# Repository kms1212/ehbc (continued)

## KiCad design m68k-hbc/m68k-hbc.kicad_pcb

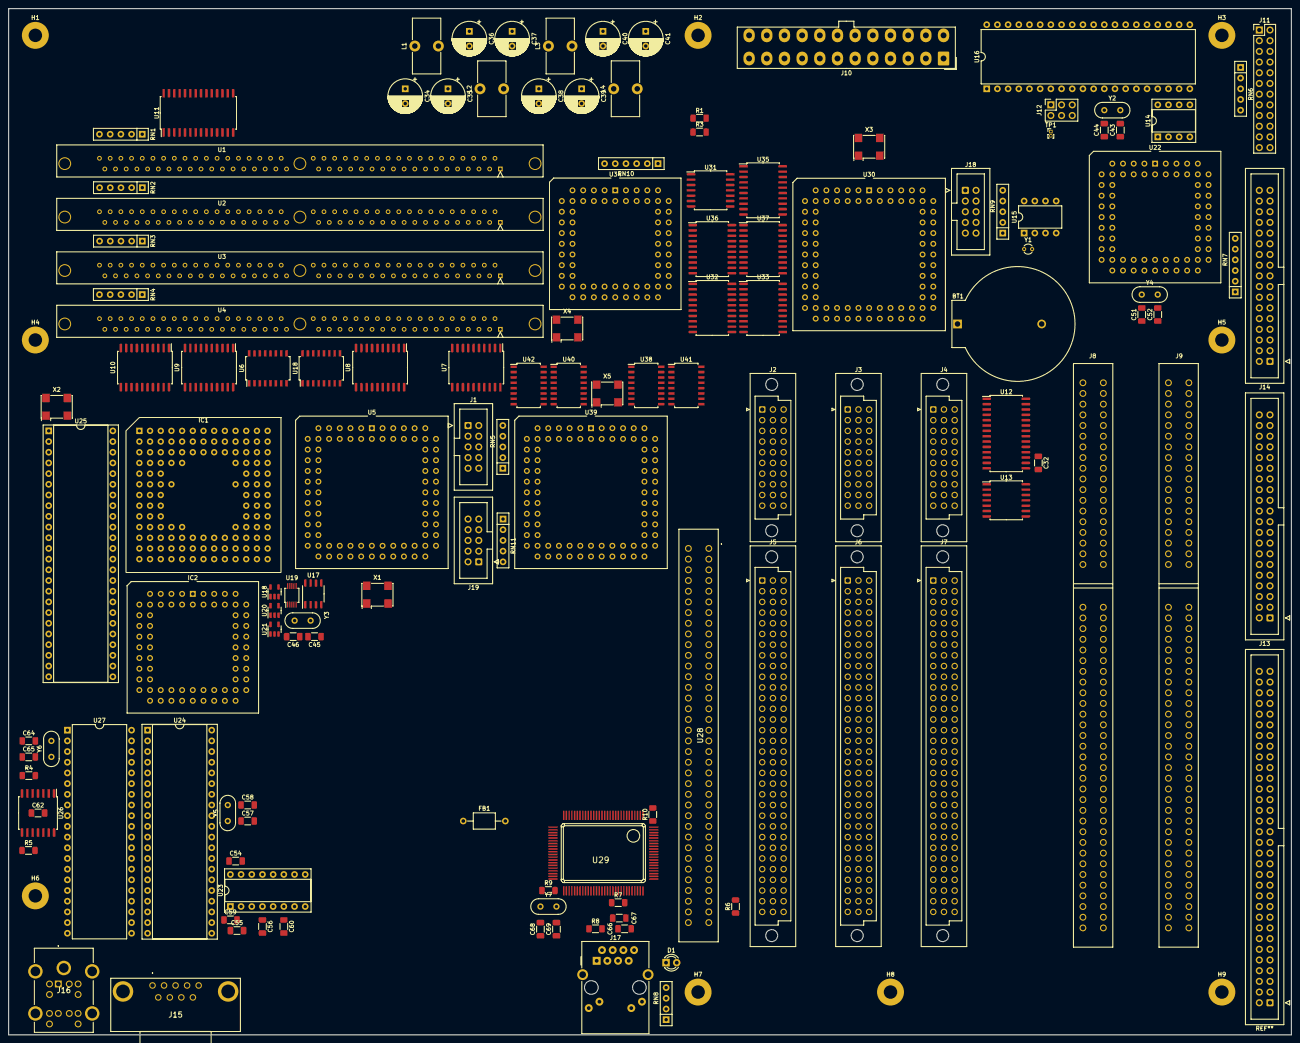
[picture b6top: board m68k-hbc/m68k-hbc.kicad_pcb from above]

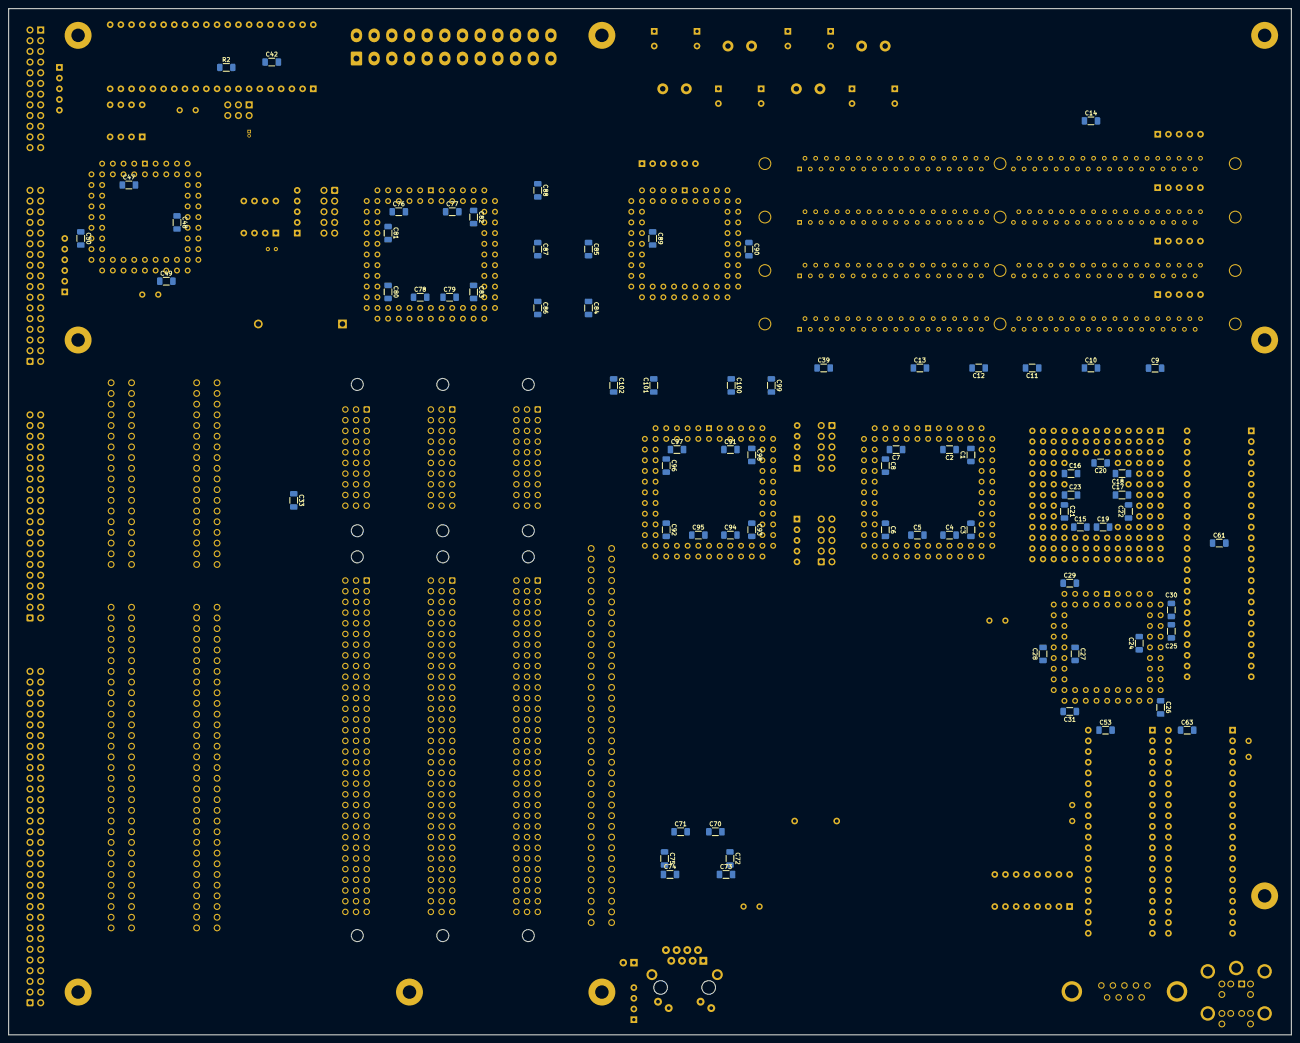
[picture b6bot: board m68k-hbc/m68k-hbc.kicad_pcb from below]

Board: 6 copper layers, 304.8 x 243.8 mm, 217 parts (75 on the bottom side), 360 nets, no tracks yet.

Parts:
BT1: Battery_Cell; BatteryHolder_ComfortableElectronic_CH273-2450_1x2450
C1, C2, C3, C4, C5, C6, C7, C8, C9, C10, C11, C12, C13, C14, C15, C16, C17, C18, C19, C20, C21, C22, C23, C24, C25, C26, C27, C28, C29, C30, C31, C32, C33, C39#2, C42, C47, C48, C49, C50, C53, C61, C62, C63, C76, C77, C78, C79, C80, C81, C82, C83, C84, C85, C86, C87, C88, C89, C90, C91, C92, C93, C94, C95, C96, C97, C98, C99, C100, C101, C102: 100p; C_1206_3216Metric_Pad1.33x1.80mm_HandSolder
C34, C36, C38, C40: 470u; CP_Radial_D8.0mm_P3.50mm
C35, C37, C39, C41: 47u; CP_Radial_D8.0mm_P3.50mm
C43, C44, C45, C46, C68, C69: 22p; C_1206_3216Metric_Pad1.33x1.80mm_HandSolder
C51, C52, C57, C58: 10p; C_1206_3216Metric_Pad1.33x1.80mm_HandSolder
C54, C55, C56, C59, C60: 1u; C_1206_3216Metric_Pad1.33x1.80mm_HandSolder
C64, C65: 20p; C_1206_3216Metric_Pad1.33x1.80mm_HandSolder
C66, C67: 10n; C_1206_3216Metric_Pad1.33x1.80mm_HandSolder
C70, C71, C72, C73, C74, C75: 100n; C_1206_3216Metric_Pad1.33x1.80mm_HandSolder
D1: LED; LED_D3.0mm
FB1: FerriteBead; L_Axial_L5.0mm_D3.6mm_P10.00mm_Horizontal_Murata_BL01RN1A2A2
H1, H2, H3, H4, H5, H6, H7, H8, H9: M3_MH_Pad; MountingHole_3.2mm_M3_Pad
IC1: MC68030RC; PGA128
IC2: MC68881FN; PLCC-68_THT-Socket
J1: JTAG_DRAMC; IDC-Header_2x05_P2.54mm_Vertical
J2, J3, J4: PEP_Power_DIN41612_3x10; DIN41612_C3_3x10_Female_Vertical_THT
J5, J6, J7: PEP_Data_DIN41612_3x32; DIN41612_C_3x32_Female_Vertical_THT
J8, J9: Bus_ISA_16bit; ISA_16bit
J10: ATX-24; Molex_Mini-Fit_Jr_5566-24A_2x12_P4.20mm_Vertical
J11: Conn_02x12_Odd_Even; PinHeader_2x12_P2.54mm_Vertical
J12: ICSP_SMC; PinSocket_2x03_P2.54mm_Vertical
J13: IDC_PATA; IDC-Header_2x20_P2.54mm_Vertical
J14: IDC_FDD; IDC-Header_2x17_P2.54mm_Vertical
J15: 5747840-4; 57478404
J16: KMDGX-6SG_P-S4N; KMDGX6SGPS4N
J17: RJ45_Amphenol_RJMG1BD3B8K1ANR
J18: JTAG_PIC; IDC-Header_2x05_P2.54mm_Vertical
J19: JTAG_ADDEC; IDC-Header_2x05_P2.54mm_Vertical
L1, L2, L3, L4: 10u; L_Toroid_Vertical_L13.0mm_W6.5mm_P5.60mm
R1, R2, R4, R5, R6, R7: 10k; R_1206_3216Metric_Pad1.30x1.75mm_HandSolder
R3: 200k; R_1206_3216Metric_Pad1.30x1.75mm_HandSolder
R8: 200; R_1206_3216Metric_Pad1.30x1.75mm_HandSolder
R9: 1M; R_1206_3216Metric_Pad1.30x1.75mm_HandSolder
R10: 27k; R_1206_3216Metric_Pad1.30x1.75mm_HandSolder
RN1, RN2, RN3, RN4: 1k; R_Array_SIP5
RN5, RN6, RN9, RN11: 10k; R_Array_SIP5
RN7, RN10: 1k; R_Array_SIP6
RN8: 330; R_Array_SIP4
TP1: TestPoint_2Pole; PinHeader_1x02_P1.00mm_Vertical
U1: SIMM72 Slot A; SIM72
U2: SIMM72 Slot B; SIM72
U3: SIMM72 Slot C; SIM72
U4: SIMM72 Slot D; SIM72
U5: EPM7128SLC84 / DRAM Controller; PLCC-84_THT-Socket
U6, U18, U38, U40, U42: 74LS137; SOIC-16W_5.3x10.2mm_P1.27mm
U7, U8, U9, U10, U32, U35, U36: 74LS245; SOIC-20W_7.5x12.8mm_P1.27mm
U11, U12: MCP23017_SO; SOIC-28W_7.5x17.9mm_P1.27mm
U13: 74LS02; SOIC-14W_7.5x9mm_P1.27mm
U14: 25LCxxx; DIP-8_W7.62mm_Socket
U15: DS1307+; DIP-8_W7.62mm
U16: ATmegA32-16P; DIP-40_W15.24mm
U17: PCA9306D; SO-8_3.9x4.9mm_P1.27mm
U18#2, U20, U21: SN74LV1T34DBV; SOT-23-5
U19: Si5351A-B-GT; MSOP-10_3x3mm_P0.5mm
U22: PC8477BV; PLCC-68_THT-Socket
U23: MAX232; DIP-16_W7.62mm_Socket
U24: 68681; DIP-40_W15.24mm_Socket
U25: 68230; DIP-48_W15.24mm_Socket
U26: 74LS06; SOIC-14W_7.5x9mm_P1.27mm
U27: VT82C42; DIP-40_W15.24mm
U28: FWMC; 55308438
U29: RTL8019AS
U30: EPM7128SLC84 / Programmable Interrupt Controller; PLCC-84_THT-Socket
U31: 74LS04; SOIC-14W_7.5x9mm_P1.27mm
U33, U37: 74LS573; SOIC-20W_7.5x12.8mm_P1.27mm
U34: MC68440FN; PLCC-68_THT-Socket
U39: EPM7128SLC84 / Address Decoder; PLCC-84_THT-Socket
U41: 74LS139; SOIC-16W_5.3x10.2mm_P1.27mm
X1, X3, X5: 70M; Oscillator_SMD_SeikoEpson_SG8002CA-4Pin_7.0x5.0mm
X2: 8M; Oscillator_SMD_SeikoEpson_SG8002CA-4Pin_7.0x5.0mm
X4: 10M; Oscillator_SMD_SeikoEpson_SG8002CA-4Pin_7.0x5.0mm
Y1: 32.768k; Crystal_Round_D2.0mm_Vertical
Y2: 16M; Crystal_HC52-6mm_Vertical
Y3: 25M; Crystal_HC52-6mm_Vertical
Y4: 24M; Crystal_HC52-6mm_Vertical
Y5: 3.6864M; Crystal_HC52-6mm_Vertical
Y6: 8M; Crystal_HC52-6mm_Vertical
Y7: 20M; Crystal_HC52-6mm_Vertical

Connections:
+3.3V: C41.1, J2.a8 (+3.3V), J2.a9 (+3.3V), J2.b8 (+3.3V), J2.b9 (+3.3V), J2.c8 (+3.3V), J2.c9 (+3.3V), J3.a8 (+3.3V), J3.a9 (+3.3V), J3.b8 (+3.3V), J3.b9 (+3.3V), J3.c8 (+3.3V), J3.c9 (+3.3V), J4.a8 (+3.3V), J4.a9 (+3.3V), J4.b8 (+3.3V), J4.b9 (+3.3V), J4.c8 (+3.3V), J4.c9 (+3.3V), L4.2, U17.2 (VREF1), U19.1 (VDD), U19.7 (VDDO)
+5V: C1.1, C2.1, C3.1, C4.2, C5.2, C6.2, C7.1, C8.2, C9.1, C10.1, C11.1, C12.1, C13.1, C14.2, C15.2, C16.2, C17.1, C18.1, C19.1, C20.1, C21.2, C22.1, C23.2, C24.1, C25.2, C26.1, C27.1, C28.1, C29.1, C30.1, C31.1, C32.2, C33.1, C37.1, C39#2.1, C42.1, C47.1, C48.1, C49.2, C50.2, C53.1, C54.1, C59.1, C61.2, C62.2, C63.1, C70.1, C71.1, C72.2, C73.2, C74.2, C75.1, C76.1, C77.1, C78.2, C79.2, C80.2, C81.2, C82.1, C83.1, C84.1, C85.1, C86.1, C87.1, C88.1, C89.1, C90.2, C91.1, C92.2, C93.1, C94.2, C95.2, C96.2, C97.1, C98.1, C99.1, C100.1, C101.1, C102.1, IC1.C06 (VCC@1), IC1.D04 (VCC@2), IC1.D10 (VCC@3), IC1.F02 (VCC@4), IC1.F11 (VCC@5), IC1.H03 (VCC@6), IC1.H11 (VCC@7), IC1.K04 (VCC@8), IC1.K10 (VCC@9), IC1.L06 (VCC@10), IC2.10 (VCC@1), IC2.16 (VCC@2), IC2.17 (VCC@3), IC2.18 (SIZE), IC2.26 (A0), IC2.27 (VCC@4), IC2.43 (VCC@5), IC2.52 (VCC@6), IC2.53 (VCC@7), IC2.61 (VCC@8), J1.4, J2.a5 (+5V), J2.a6 (+5V), J2.a7 (+5V), J2.b7 (+5V), J2.c5 (+5V), J2.c6 (+5V), J2.c7 (+5V), J3.a5 (+5V), J3.a6 (+5V), J3.a7 (+5V), J3.b7 (+5V), J3.c5 (+5V), J3.c6 (+5V), J3.c7 (+5V), J4.a5 (+5V), J4.a6 (+5V), J4.a7 (+5V), J4.b7 (+5V), J4.c5 (+5V), J4.c6 (+5V), J4.c7 (+5V), J8.3 (+5V), J8.78 (+5V), J9.3 (+5V), J9.78 (+5V), J11.23, J16.A5, J16.B5, J18.4, J19.4, L2.2, R1.1, R3.1, R6.1, RN1.1 (common), RN2.1 (common), RN3.1 (common), RN4.1 (common), RN5.1 (common), RN6.1 (common), RN7.1 (common), RN8.1 (common), RN9.1 (common), RN10.1 (common), RN11.1 (common), TP1.2, U1.10 (+5V), U1.30 (+5V), U1.59 (+5B), U2.10 (+5V), U2.30 (+5V), U2.59 (+5B), U3.10 (+5V), U3.30 (+5V), U3.59 (+5B), U4.10 (+5V), U4.30 (+5V), U4.59 (+5B), U5.3 (VCCINT_2), U5.13 (VCCIO_2), U5.26 (VCCIO_3), U5.38 (VCCIO_4), U5.43 (VCCINT), U5.53 (VCCIO_5), U5.66 (VCCIO_6), U5.78 (VCCIO), U6.6 (G1), U6.16 (VCC), U7.20 (VCC), U8.20 (VCC), U9.20 (VCC), U10.20 (VCC), U11.9 (VDD), U12.9 (VDD), U12.15 (A0), U13.14 (VCC), U14.3 (~WP), U14.7 (~HOLD), U14.8 (VCC), U15.8 (VCC), U18.6 (G1), U18.16 (VCC), U18#2.5 (VCC), U20.5 (VCC), U21.5 (VCC), U22.18 (+5V), U22.27 (IDENT), U22.60 (+5V), U22.68 (+5V), U23.16 (VCC), U24.40 (VCC), U25.12 (VCC), U26.14 (VCC), U27.40 (+5V), U28.1 (+5V), U28.2 (+5V), U28.3 (+5V), U28.4 (+5V), U28.69 (+5V), U28.70 (+5V), U28.71 (+5V), U28.72 (+5V), U29.6 (VDD), U29.15 (SA8), U29.16 (SA9), U29.17 (VDD2), U29.31 (SMEMRB), U29.32 (SMEMWB), U29.47 (VDD3), U29.57 (VDD4), U29.65 (JP), U29.70 (VDD5), U29.89 (VDD6), U30.3 (VCCINT_2), U30.13 (VCCIO_2), U30.26 (VCCIO_3), U30.38 (VCCIO_4), U30.43 (VCCINT), U30.53 (VCCIO_5), U30.66 (VCCIO_6), U30.78 (VCCIO), U31.14 (VCC), U32.20 (VCC), U33.20 (VCC), U34.20 (+5V), U34.55 (+5V), U35.20 (VCC), U36.20 (VCC), U37.20 (VCC), U38.6 (G1), U38.16 (VCC), U39.3 (VCCINT_2), U39.13 (VCCIO_2), U39.26 (VCCIO_3), U39.38 (VCCIO_4), U39.43 (VCCINT), U39.53 (VCCIO_5), U39.66 (VCCIO_6), U39.78 (VCCIO), U40.6 (G1), U40.16 (VCC), U41.16 (VCC), U42.6 (G1), U42.16 (VCC), X1.4 (Vcc), X2.4 (Vcc), X3.4 (Vcc), X4.4 (Vcc), X5.4 (Vcc)
+5VP: C39.1, J2.a4 (+5VSB), J3.a4 (+5VSB), J4.a4 (+5VSB), L3.2, R2.1, U16.10 (VCC)
+12V: C35.1, J2.a2 (+12V), J2.a3 (+12V), J2.b2 (+12V), J2.b3 (+12V), J2.c2 (+12V), J2.c3 (+12V), J3.a2 (+12V), J3.a3 (+12V), J3.b2 (+12V), J3.b3 (+12V), J3.c2 (+12V), J3.c3 (+12V), J4.a2 (+12V), J4.a3 (+12V), J4.b2 (+12V), J4.b3 (+12V), J4.c2 (+12V), J4.c3 (+12V), J8.9 (+12V), J9.9 (+12V), L1.2
+BATT: BT1.1 (+), U15.3 (VBAT)
-5V: J2.c4 (-5V), J3.c4 (-5V), J4.c4 (-5V), J8.5 (-5V), J9.5 (-5V)
-12V: J2.b4 (-12V), J3.b4 (-12V), J4.b4 (-12V), J8.7 (-12V), J9.7 (-12V), J10.14 (-12V)
/ADDEC/ADDEC_TCK: J19.1, RN11.5 (R4), U39.62 (IO/TCK)
/ADDEC/ADDEC_TDI: J19.9, RN11.2 (R1), U39.14 (IO/TDI)
/ADDEC/ADDEC_TDO: J19.3, RN11.4 (R3), U39.71 (IO/TDO)
/ADDEC/ADDEC_TMS: J19.5, RN11.3 (R2), U39.23 (IO/TMS)
/ADDEC/CS0: U38.1 (A0), U39.9 (IO_6), U40.1 (A0), U42.1 (A0)
/ADDEC/CS1: U38.2 (A1), U39.8 (IO_5), U40.2 (A1), U42.2 (A1)
/ADDEC/CS2: U38.3 (A2), U39.6 (IO_4), U40.3 (A2), U42.3 (A2)
/ADDEC/CS3: U39.5 (IO_3), U41.2 (A0)
/ADDEC/CS4: U39.4 (IO_2), U41.3 (A1)
/ADDEC/~CSE: U38.4 (~GL), U39.81 (IO), U40.4 (~GL), U41.1 (E), U42.4 (~GL)
/ADDEC/~DEC0: U38.5 (~G2), U41.4 (O0)
/ADDEC/~DEC1: U40.5 (~G2), U41.5 (O1)
/ADDEC/~DEC2: U41.6 (O2), U42.5 (~G2)
/DMAC/A8/D0: U34.51 (A8/D0), U36.2 (A0), U37.2 (D0)
/DMAC/A9/D1: U34.50 (A9/D1), U36.3 (A1), U37.3 (D1)
/DMAC/A10/D2: U34.49 (A10/D2), U36.4 (A2), U37.4 (D2)
/DMAC/A11/D3: U34.48 (A11/D3), U36.5 (A3), U37.5 (D3)
/DMAC/A12/D4: U34.47 (A12/D4), U36.6 (A4), U37.6 (D4)
/DMAC/A13/D5: U34.46 (A13/D5), U36.7 (A5), U37.7 (D5)
/DMAC/A14/D6: U34.45 (A14/D6), U36.8 (A6), U37.8 (D6)
/DMAC/A15/D7: U34.44 (A15/D7), U36.9 (A7), U37.9 (D7)
/DMAC/A16/D8: U32.2 (A0), U33.2 (D0), U34.43 (A16/D8)
/DMAC/A17/D9: U32.3 (A1), U33.3 (D1), U34.42 (A17/D9)
/DMAC/A18/D10: U32.4 (A2), U33.4 (D2), U34.41 (A18/D10)
/DMAC/A19/D11: U32.5 (A3), U33.5 (D3), U34.40 (A19/D11)
/DMAC/A20/D12: U32.6 (A4), U33.6 (D4), U34.39 (A20/D12)
/DMAC/A21/D13: U32.7 (A5), U33.7 (D5), U34.38 (A21/D13)
/DMAC/A22/D14: U32.8 (A6), U33.8 (D6), U34.37 (A22/D14)
/DMAC/A23/D15: U32.9 (A7), U33.9 (D7), U34.36 (A23/D15)
/DMAC/UAS: U31.2, U33.11 (Load), U37.11 (Load)
/DMAC/~DBEN: RN10.4 (R3), U32.19 (CE), U34.67 (~DBEN), U36.19 (CE)
/DMAC/~DDIR: RN10.5 (R4), U32.1 (A->B), U34.1 (~DDIR), U36.1 (A->B)
/DMAC/~HIBYTE: RN10.6 (R5), U34.66 (~HIBYTE), U35.19 (CE)
/DMAC/~OWN: RN10.2 (R1), U33.1 (OE), U34.64 (~OWN), U37.1 (OE)
/DMAC/~UAS: RN10.3 (R2), U31.1, U34.65 (~UAS)
/DRAM/DRAMC_TCK: J1.1, RN5.5 (R4), U5.62 (IO/TCK)
/DRAM/DRAMC_TDI: J1.9, RN5.2 (R1), U5.14 (IO/TDI)
/DRAM/DRAMC_TDO: J1.3, RN5.4 (R3), U5.71 (IO/TDO)
/DRAM/DRAMC_TMS: J1.5, RN5.3 (R2), U5.23 (IO/TMS)
/DRAM/RASS0: U5.12 (IO_9), U6.1 (A0), U18.1 (A0)
/DRAM/RASS1: U5.11 (IO_8), U6.2 (A1), U18.2 (A1)
/DRAM/RASS2: U5.10 (IO_7), U6.3 (A2), U18.3 (A2)
/DRAM/SA0: U1.12 (A0), U2.12 (A0), U3.12 (A0), U4.12 (A0), U5.68 (IO_51)
/DRAM/SA1: U1.13 (A1), U2.13 (A1), U3.13 (A1), U4.13 (A1), U5.67 (IO_50)
/DRAM/SA2: U1.14 (A2), U2.14 (A2), U3.14 (A2), U4.14 (A2), U5.69 (IO_52)
/DRAM/SA3: U1.15 (A3), U2.15 (A3), U3.15 (A3), U4.15 (A3), U5.70 (IO_53)
/DRAM/SA4: U1.16 (A4), U2.16 (A4), U3.16 (A4), U4.16 (A4), U5.73 (IO_54)
/DRAM/SA5: U1.17 (A5), U2.17 (A5), U3.17 (A5), U4.17 (A5), U5.74 (IO_55)
/DRAM/SA6: U1.18 (A6), U2.18 (A6), U3.18 (A6), U4.18 (A6), U5.75 (IO_56)
/DRAM/SA7: U1.28 (A7), U2.28 (A7), U3.28 (A7), U4.28 (A7), U5.77 (IO_58)
/DRAM/SA8: U1.31 (A8), U2.31 (A8), U3.31 (A8), U4.31 (A8), U5.80 (IO_60)
/DRAM/SA9: U1.32 (A9), U2.32 (A9), U3.32 (A9), U4.32 (A9), U5.81 (IO)
/DRAM/SA10: U1.19 (A10), U2.19 (A10), U3.19 (A10), U4.19 (A10), U5.76 (IO_57)
/DRAM/SA11: U1.29 (A11), U2.29 (A11), U3.29 (A11), U4.29 (A11), U5.79 (IO_59)
/DRAM/SDQ0: U1.2 (DQ0), U2.2 (DQ0), U3.2 (DQ0), U4.2 (DQ0), U7.2 (A0)
/DRAM/SDQ1: U1.4 (DQ1), U2.4 (DQ1), U3.4 (DQ1), U4.4 (DQ1), U7.4 (A2)
/DRAM/SDQ2: U1.6 (DQ2), U2.6 (DQ2), U3.6 (DQ2), U4.6 (DQ2), U7.6 (A4)
/DRAM/SDQ3: U1.8 (DQ3), U2.8 (DQ3), U3.8 (DQ3), U4.8 (DQ3), U7.8 (A6)
/DRAM/SDQ4: U1.20 (DQ4), U2.20 (DQ4), U3.20 (DQ4), U4.20 (DQ4), U8.2 (A0)
/DRAM/SDQ5: U1.22 (DQ5), U2.22 (DQ5), U3.22 (DQ5), U4.22 (DQ5), U8.4 (A2)
/DRAM/SDQ6: U1.24 (DQ6), U2.24 (DQ6), U3.24 (DQ6), U4.24 (DQ6), U8.6 (A4)
/DRAM/SDQ7: U1.26 (DQ7), U2.26 (DQ7), U3.26 (DQ7), U4.26 (DQ7), U8.8 (A6)
/DRAM/SDQ8: U1.49 (DQ8), U2.49 (DQ8), U3.49 (DQ8), U4.49 (DQ8), U9.2 (A0)
/DRAM/SDQ9: U1.51 (DQ9), U2.51 (DQ9), U3.51 (DQ9), U4.51 (DQ9), U9.4 (A2)
/DRAM/SDQ10: U1.53 (DQ10), U2.53 (DQ10), U3.53 (DQ10), U4.53 (DQ10), U9.6 (A4)
/DRAM/SDQ11: U1.55 (DQ11), U2.55 (DQ11), U3.55 (DQ11), U4.55 (DQ11), U9.8 (A6)
/DRAM/SDQ12: U1.57 (DQ12), U2.57 (DQ12), U3.57 (DQ12), U4.57 (DQ12), U10.2 (A0)
/DRAM/SDQ13: U1.61 (DQ13), U2.61 (DQ13), U3.61 (DQ13), U4.61 (DQ13), U10.4 (A2)
/DRAM/SDQ14: U1.63 (DQ14), U2.63 (DQ14), U3.63 (DQ14), U4.63 (DQ14), U10.6 (A4)
/DRAM/SDQ15: U1.65 (DQ15), U2.65 (DQ15), U3.65 (DQ15), U4.65 (DQ15), U10.8 (A6)
/DRAM/SDQ16: U1.3 (DQ16), U2.3 (DQ16), U3.3 (DQ16), U4.3 (DQ16), U7.3 (A1)
/DRAM/SDQ17: U1.5 (DQ17), U2.5 (DQ17), U3.5 (DQ17), U4.5 (DQ17), U7.5 (A3)
/DRAM/SDQ18: U1.7 (DQ18), U2.7 (DQ18), U3.7 (DQ18), U4.7 (DQ18), U7.7 (A5)
/DRAM/SDQ19: U1.9 (DQ19), U2.9 (DQ19), U3.9 (DQ19), U4.9 (DQ19), U7.9 (A7)
/DRAM/SDQ20: U1.21 (DQ20), U2.21 (DQ20), U3.21 (DQ20), U4.21 (DQ20), U8.3 (A1)
/DRAM/SDQ21: U1.23 (DQ21), U2.23 (DQ21), U3.23 (DQ21), U4.23 (DQ21), U8.5 (A3)
/DRAM/SDQ22: U1.25 (DQ22), U2.25 (DQ22), U3.25 (DQ22), U4.25 (DQ22), U8.7 (A5)
/DRAM/SDQ23: U1.27 (DQ23), U2.27 (DQ23), U3.27 (DQ23), U4.27 (DQ23), U8.9 (A7)
/DRAM/SDQ24: U1.50 (DQ24), U2.50 (DQ24), U3.50 (DQ24), U4.50 (DQ24), U9.3 (A1)
/DRAM/SDQ25: U1.52 (DQ25), U2.52 (DQ25), U3.52 (DQ25), U4.52 (DQ25), U9.5 (A3)
/DRAM/SDQ26: U1.54 (DQ26), U2.54 (DQ26), U3.54 (DQ26), U4.54 (DQ26), U9.7 (A5)
/DRAM/SDQ27: U1.56 (DQ27), U2.56 (DQ27), U3.56 (DQ27), U4.56 (DQ27), U9.9 (A7)
/DRAM/SDQ28: U1.58 (DQ28), U2.58 (DQ28), U3.58 (DQ28), U4.58 (DQ28), U10.3 (A1)
/DRAM/SDQ29: U1.60 (DQ29), U2.60 (DQ29), U3.60 (DQ29), U4.60 (DQ29), U10.5 (A3)
/DRAM/SDQ30: U1.62 (DQ30), U2.62 (DQ30), U3.62 (DQ30), U4.62 (DQ30), U10.7 (A5)
/DRAM/SDQ31: U1.64 (DQ31), U2.64 (DQ31), U3.64 (DQ31), U4.64 (DQ31), U10.9 (A7)
/DRAM/~MMAP0: RN1.2 (R1), U1.67 (P0), U11.1 (GPB0)
/DRAM/~MMAP1: RN1.3 (R2), U1.68 (P1), U11.2 (GPB1)
/DRAM/~MMAP2: RN1.4 (R3), U1.69 (P2), U11.3 (GPB2)
/DRAM/~MMAP3: RN1.5 (R4), U1.70 (P3), U11.4 (GPB3)
/DRAM/~MMBP0: RN2.2 (R1), U2.67 (P0), U11.8 (GPB7)
/DRAM/~MMBP1: RN2.3 (R2), U2.68 (P1), U11.7 (GPB6)
/DRAM/~MMBP2: RN2.4 (R3), U2.69 (P2), U11.6 (GPB5)
/DRAM/~MMBP3: RN2.5 (R4), U2.70 (P3), U11.5 (GPB4)
/DRAM/~MMCAS0: U1.40 (~CAS0), U2.40 (~CAS0), U3.40 (~CAS0), U4.40 (~CAS0), U5.4 (IO_2)
/DRAM/~MMCAS1: U1.43 (~CAS1), U2.43 (~CAS1), U3.43 (~CAS1), U4.43 (~CAS1), U5.8 (IO_5)
/DRAM/~MMCAS2: U1.41 (~CAS2), U2.41 (~CAS2), U3.41 (~CAS2), U4.41 (~CAS2), U5.5 (IO_3)
/DRAM/~MMCAS3: U1.42 (~CAS3), U2.42 (~CAS3), U3.42 (~CAS3), U4.42 (~CAS3), U5.6 (IO_4)
/DRAM/~MMCP0: RN3.2 (R1), U3.67 (P0), U11.25 (GPA4)
/DRAM/~MMCP1: RN3.3 (R2), U3.68 (P1), U11.26 (GPA5)
/DRAM/~MMCP2: RN3.4 (R3), U3.69 (P2), U11.27 (GPA6)
/DRAM/~MMCP3: RN3.5 (R4), U3.70 (P3), U11.28 (GPA7)
/DRAM/~MMDP0: RN4.2 (R1), U4.67 (P0), U11.21 (GPA0)
/DRAM/~MMDP1: RN4.3 (R2), U4.68 (P1), U11.22 (GPA1)
/DRAM/~MMDP2: RN4.4 (R3), U4.69 (P2), U11.23 (GPA2)
/DRAM/~MMDP3: RN4.5 (R4), U4.70 (P3), U11.24 (GPA3)
/DRAM/~MMRAS0_A: U1.44 (~RAS0), U1.45 (~RAS2), U6.7 (Y7)
/DRAM/~MMRAS0_B: U2.44 (~RAS0), U2.45 (~RAS2), U6.9 (Y6)
/DRAM/~MMRAS0_C: U3.44 (~RAS0), U3.45 (~RAS2), U6.10 (Y5)
/DRAM/~MMRAS0_D: U4.44 (~RAS0), U4.45 (~RAS2), U6.11 (Y4)
/DRAM/~MMRAS1_A: U1.33 (~RAS3), U1.34 (~RAS1), U6.12 (Y3), U18.7 (Y7)
/DRAM/~MMRAS1_B: U2.33 (~RAS3), U2.34 (~RAS1), U6.13 (Y2), U18.9 (Y6)
/DRAM/~MMRAS1_C: U3.33 (~RAS3), U3.34 (~RAS1), U6.14 (Y1), U18.10 (Y5)
/DRAM/~MMRAS1_D: U4.33 (~RAS3), U4.34 (~RAS1), U6.15 (Y0), U18.11 (Y4)
/DRAM/~RASS_L: U5.15 (IO_10), U6.4 (~GL), U18.4 (~GL)
/Disk/~RD: J13.23 (~DIOW), U22.4 (~RD)
/Disk/~WR: J13.25 (~DIOR), U22.5 (~WR)
/Ethernet/LED0: J17.L3 (LEDG_K), U29.61 (LED0)
/Ethernet/LED1: J17.L2 (LEDY_K), U29.62 (LED1)
/Ethernet/LED2: D1.1 (K), U29.63 (LED2)
/Ethernet/RX+: J17.R3 (RD+), U29.59 (TPIN+)
/Ethernet/RX-: J17.R6 (RD-), U29.58 (TPIN-)
/Ethernet/TX+: J17.R1 (TD+), R8.1, U29.45 (TPOUT+)
/Ethernet/TX-: J17.R2 (TD-), R8.2, U29.46 (TPOUT-)
/FWMEM/~FWMPRES: R6.2, U28.67 (~PRES)
/IO/KBCLK: J16.A6, J16.B6, U26.6, U27.1 (TEST0)
/IO/KBDAT: J16.A1, R5.1, U26.8, U27.27 (P10)
/IO/MSCLK: R4.2, U26.4, U27.39 (TEST1)
/IO/MSDAT: J16.B1, U26.2, U27.28 (P11)
/IO/~DTACK8: U24.9 (DTACK), U25.42 (DTACK)
/PEP/~P0PRESA: J2.b6 (~PRES), U13.2
/PEP/~P0PRESB: J5.a2 (~PRES), U13.3
/PEP/~P0PRES: U12.1 (GPB0), U13.1
/PEP/~P1PRESA: J3.b6 (~PRES), U13.5
/PEP/~P1PRESB: J6.a2 (~PRES), U13.6
/PEP/~P1PRES: U12.2 (GPB1), U13.4
/PEP/~P2PRESA: J4.b6 (~PRES), U13.8
/PEP/~P2PRESB: J7.a2 (~PRES), U13.9
/PEP/~P2PRES: U12.3 (GPB2), U13.10
/PIC/PIC_TCK: J18.1, RN9.5 (R4), U30.62 (IO/TCK)
/PIC/PIC_TDI: J18.9, RN9.2 (R1), U30.14 (IO/TDI)
/PIC/PIC_TDO: J18.3, RN9.4 (R3), U30.71 (IO/TDO)
/PIC/PIC_TMS: J18.5, RN9.3 (R2), U30.23 (IO/TMS)
/Power/+3.3VI: C40.1, J10.1 (+3.3V), J10.2 (+3.3V), J10.12 (+3.3V), J10.13 (+3.3V), L4.1
/Power/+5VI: C36.1, J10.4 (+5V), J10.6 (+5V), J10.21 (+5V), J10.22 (+5V), J10.23 (+5V), L2.1
/Power/+5VSBI: C38.1, J10.9 (+5VSB), L3.1
/Power/+12VI: C34.1, J10.10 (+12V), J10.11 (+12V), L1.1
/SMC/SCL33: U17.3 (SCL1), U19.4 (SCL)
/SMC/SDA33: U17.4 (SDA1), U19.5 (SDA)
/SMC/SMC_MISO: J12.1, U14.2 (MISO), U16.7 (PB6)
/SMC/SMC_MOSI: J12.4, U14.5 (MOSI), U16.6 (PB5)
/SMC/SMC_SCK: J12.3, U14.6 (SCK), U16.8 (PB7)
A0: IC1.A02 (A0), J5.b24 (A0), J6.b24 (A0), J7.b24 (A0), J8.62 (BA00), J9.62 (BA00), J13.35 (DA0), U5.28 (IO_20), U22.7 (A0), U24.1 (RS1), U25.29 (RS1), U27.9 (A0), U30.73 (IO_54), U34.14 (~UDS/A0), U39.28 (IO_20)
A1: IC1.C04 (A1), IC2.25 (A1), J5.b25 (A1), J6.b25 (A1), J7.b25 (A1), J8.61 (BA01), J9.61 (BA01), J13.33 (DA1), U5.50 (IO_37), U22.8 (A1), U24.3 (RS2), U25.28 (RS2), U28.16 (A1), U29.5 (SA0), U30.74 (IO_55), U34.61 (A1), U39.50 (IO_37)
A2: IC1.D13 (A2), IC2.24 (A2), J5.b26 (A2), J6.b26 (A2), J7.b26 (A2), J8.60 (BA02), J9.60 (BA02), J13.36 (DA2), U5.37 (IO_28), U22.10 (A2), U24.5 (RS3), U25.27 (RS3), U28.18 (A2), U29.7 (SA1), U30.75 (IO_56), U34.60 (A2), U39.37 (IO_28)
A3: IC1.D12 (A3), IC2.23 (A3), J5.b27 (A3), J6.b27 (A3), J7.b27 (A3), J8.59 (BA03), J9.59 (BA03), U5.35 (IO_26), U24.6 (RS4), U25.26 (RS4), U28.20 (A3), U29.8 (SA2), U30.76 (IO_57), U34.59 (A3), U39.35 (IO_26)
A4: IC1.C13 (A4), IC2.22 (A4), J5.b28 (A4), J6.b28 (A4), J7.b28 (A4), J8.58 (BA04), J9.58 (BA04), U5.51 (IO_38), U25.25 (RS5), U28.22 (A4), U29.9 (SA3), U30.77 (IO_58), U34.58 (A4), U39.51 (IO_38)
A5: IC1.C12 (A5), J5.b29 (A5), J6.b29 (A5), J7.b29 (A5), J8.57 (BA05), J9.57 (BA05), U5.49 (IO_36), U28.24 (A5), U29.10 (SA4), U30.79 (IO_59), U34.57 (A5), U39.49 (IO_36)
A6: IC1.D11 (A6), J5.b30 (A6), J6.b30 (A6), J7.b30 (A6), J8.56 (BA06), J9.56 (BA06), U5.33 (IO_24), U28.26 (A6), U30.80 (IO_60), U34.56 (A6), U39.33 (IO_24)
A7: IC1.B13 (A7), J5.b31 (A7), J6.b31 (A7), J7.b31 (A7), J8.55 (BA07), J9.55 (BA07), U5.48 (IO_35), U28.28 (A7), U30.81 (IO), U34.54 (A7), U39.48 (IO_35)
A8: IC1.B12 (A8), J5.b15 (A8), J6.b15 (A8), J7.b15 (A8), J8.54 (BA08), J9.54 (BA08), U5.46 (IO_34), U28.32 (A8), U37.19 (Q0), U39.46 (IO_34)
A9: IC1.C11 (A9), J5.b16 (A9), J6.b16 (A9), J7.b16 (A9), J8.53 (BA09), J9.53 (BA09), U5.45 (IO_33), U28.34 (A9), U37.18 (Q1), U39.45 (IO_33)
A10: IC1.A13 (A10), J5.b17 (A10), J6.b17 (A10), J7.b17 (A10), J8.52 (BA10), J9.52 (BA10), U5.17 (IO_12), U28.36 (A10), U37.17 (Q2), U39.17 (IO_12)
A11: IC1.C10 (A11), J5.b18 (A11), J6.b18 (A11), J7.b18 (A11), J8.51 (BA11), J9.51 (BA11), U5.41 (IO_31), U28.38 (A11), U37.16 (Q3), U39.41 (IO_31)
A12: IC1.B11 (A12), J5.b19 (A12), J6.b19 (A12), J7.b19 (A12), J8.50 (BA12), J9.50 (BA12), U5.44 (IO_32), U28.40 (A12), U37.15 (Q4), U39.44 (IO_32)
A13: IC1.A12 (A13), J5.b20 (A13), J6.b20 (A13), J7.b20 (A13), J8.49 (BA13), J9.49 (BA13), U5.16 (IO_11), U28.42 (A13), U37.14 (Q5), U39.16 (IO_11)
A14: IC1.B10 (A14), J5.b21 (A14), J6.b21 (A14), J7.b21 (A14), J8.48 (BA14), J9.48 (BA14), U5.40 (IO_30), U28.44 (A14), U37.13 (Q6), U39.40 (IO_30)
A15: IC1.A11 (A15), J5.b22 (A15), J6.b22 (A15), J7.b22 (A15), J8.47 (BA15), J9.47 (BA15), U5.18 (IO_13), U28.46 (A15), U37.12 (Q7), U39.18 (IO_13)
A16: IC1.B09 (A16), J5.b10 (A16), J6.b10 (A16), J7.b10 (A16), J8.46 (BA16), J9.46 (BA16), U5.36 (IO_27), U28.50 (A16), U33.19 (Q0), U39.36 (IO_27)
A17: IC1.A10 (A17), J5.b11 (A17), J6.b11 (A17), J7.b11 (A17), J8.45 (BA17), J8.88 (LA17), J9.45 (BA17), J9.88 (LA17), U5.21 (IO_15), U28.52 (A17), U33.18 (Q1), U39.21 (IO_15)
A18: IC1.C08 (A18), J5.b12 (A18), J6.b12 (A18), J7.b12 (A18), J8.44 (BA18), J8.87 (LA18), J9.44 (BA18), J9.87 (LA18), U5.39 (IO_29), U28.54 (A18), U33.17 (Q2), U39.39 (IO_29)
A19: IC1.A09 (A19), J5.b13 (A19), J6.b13 (A19), J7.b13 (A19), J8.43 (BA19), J8.86 (LA19), J9.43 (BA19), J9.86 (LA19), U5.20 (IO_14), U28.56 (A19), U33.16 (Q3), U39.20 (IO_14)
A20: IC1.B08 (A20), J5.b6 (A20), J6.b6 (A20), J7.b6 (A20), J8.85 (LA20), J9.85 (LA20), U5.34 (IO_25), U28.58 (A20), U33.15 (Q4), U39.34 (IO_25)
A21: IC1.A08 (A21), J5.b7 (A21), J6.b7 (A21), J7.b7 (A21), J8.84 (LA21), J9.84 (LA21), U5.22 (IO_16), U28.60 (A21), U33.14 (Q5), U39.22 (IO_16)
A22: IC1.B07 (A22), J5.b8 (A22), J6.b8 (A22), J7.b8 (A22), J8.83 (LA22), J9.83 (LA22), U5.31 (IO_23), U33.13 (Q6), U39.31 (IO_23)
A23: IC1.A07 (A23), J5.b9 (A23), J6.b9 (A23), J7.b9 (A23), J8.82 (LA23), J9.82 (LA23), U5.25 (IO_18), U33.12 (Q7), U39.25 (IO_18)
A24: IC1.A06 (A24), U5.24 (IO_17), U34.68 (A24), U39.24 (IO_17)
A25: IC1.B06 (A25), U5.30 (IO_22), U34.2 (A25), U39.30 (IO_22)
A26: IC1.A05 (A26), U5.27 (IO_19), U34.3 (A26), U39.27 (IO_19)
A27: IC1.B05 (A27), U5.29 (IO_21), U34.4 (A27), U39.29 (IO_21)
A28: IC1.A04 (A28), U34.7 (A28), U39.10 (IO_7)
A29: IC1.B04 (A29), U34.8 (A29), U39.11 (IO_8)
A30: IC1.A03 (A30), U34.25 (A30), U39.12 (IO_9)
A31: IC1.B03 (A31), U34.26 (A31), U39.15 (IO_10)
BUZ: J11.2, U16.19 (PD5)
CPUCLK: IC1.E01 (CLK), U18#2.4 (Y)
D0: IC1.K13 (D0), IC2.3 (D0), J5.a24 (D0), J6.a24 (D0), J7.a24 (D0), U7.18 (B0)
D1: IC1.K12 (D1), IC2.2 (D1), J5.a25 (D1), J6.a25 (D1), J7.a25 (D1), U7.16 (B2)
D2: IC1.L13 (D2), IC2.1 (D2), J5.a26 (D2), J6.a26 (D2), J7.a26 (D2), U7.14 (B4)
D3: IC1.M13 (D3), IC2.68 (D3), J5.a27 (D3), J6.a27 (D3), J7.a27 (D3), U7.12 (B6)
D4: IC1.L12 (D4), IC2.67 (D4), J5.a28 (D4), J6.a28 (D4), J7.a28 (D4), U8.18 (B0)
D5: IC1.K11 (D5), IC2.66 (D5), J5.a29 (D5), J6.a29 (D5), J7.a29 (D5), U8.16 (B2)
D6: IC1.M12 (D6), IC2.65 (D6), J5.a30 (D6), J6.a30 (D6), J7.a30 (D6), U8.14 (B4)
D7: IC1.L11 (D7), IC2.64 (D7), J5.a31 (D7), J6.a31 (D7), J7.a31 (D7), U8.12 (B6)
D8: IC1.N13 (D8), IC2.62 (D8), J5.a22 (D8), J6.a22 (D8), J7.a22 (D8), U9.18 (B0)
D9: IC1.M11 (D9), IC2.60 (D9), J5.a21 (D9), J6.a21 (D9), J7.a21 (D9), U9.16 (B2)
D10: IC1.L10 (D10), IC2.59 (D10), J5.a20 (D10), J6.a20 (D10), J7.a20 (D10), U9.14 (B4)
D11: IC1.N12 (D11), IC2.58 (D11), J5.a19 (D11), J6.a19 (D11), J7.a19 (D11), U9.12 (B6)
D12: IC1.M10 (D12), IC2.57 (D12), J5.a18 (D12), J6.a18 (D12), J7.a18 (D12), U10.18 (B0)
D13: IC1.N11 (D13), IC2.56 (D13), J5.a17 (D13), J6.a17 (D13), J7.a17 (D13), U10.16 (B2)
D14: IC1.M09 (D14), IC2.55 (D14), J5.a16 (D14), J6.a16 (D14), J7.a16 (D14), U10.14 (B4)
D15: IC1.N10 (D15), IC2.54 (D15), J5.a15 (D15), J6.a15 (D15), J7.a15 (D15), U10.12 (B6)
D16: IC1.N09 (D16), IC2.50 (D16), J5.c25 (D16), J6.c25 (D16), J7.c25 (D16), J8.40 (DB0), J9.40 (DB0), J13.17 (DD0), U7.17 (B1), U28.59 (D0), U29.36 (SD0), U30.15 (IO_10), U32.18 (B0), U35.2 (A0)
D17: IC1.M08 (D17), IC2.49 (D17), J5.c24 (D17), J6.c24 (D17), J7.c24 (D17), J8.39 (DB1), J9.39 (DB1), J13.15 (DD1), U7.15 (B3), U28.57 (D1), U29.37 (SD1), U30.16 (IO_11), U32.17 (B1), U35.3 (A1)
D18: IC1.N08 (D18), IC2.48 (D18), J5.c23 (D18), J6.c23 (D18), J7.c23 (D18), J8.38 (DB2), J9.38 (DB2), J13.13 (DD2), U7.13 (B5), U28.55 (D2), U29.38 (SD2), U30.17 (IO_12), U32.16 (B2), U35.4 (A2)
D19: IC1.N07 (D19), IC2.47 (D19), J5.c22 (D19), J6.c22 (D19), J7.c22 (D19), J8.37 (DB3), J9.37 (DB3), J13.11 (DD3), U7.11 (B7), U28.53 (D3), U29.39 (SD3), U30.18 (IO_13), U32.15 (B3), U35.5 (A3)
D20: IC1.M07 (D20), IC2.46 (D20), J5.c21 (D20), J6.c21 (D20), J7.c21 (D20), J8.36 (DB4), J9.36 (DB4), J13.9 (DD4), U8.17 (B1), U28.51 (D4), U29.40 (SD4), U30.20 (IO_14), U32.14 (B4), U35.6 (A4)
D21: IC1.N06 (D21), IC2.45 (D21), J5.c20 (D21), J6.c20 (D21), J7.c20 (D21), J8.35 (DB5), J9.35 (DB5), J13.7 (DD5), U8.15 (B3), U28.49 (D5), U29.41 (SD5), U30.21 (IO_15), U32.13 (B5), U35.7 (A5)
D22: IC1.M06 (D22), IC2.44 (D22), J5.c19 (D22), J6.c19 (D22), J7.c19 (D22), J8.34 (DB6), J9.34 (DB6), J13.5 (DD6), U8.13 (B5), U28.47 (D6), U29.42 (SD6), U30.22 (IO_16), U32.12 (B6), U35.8 (A6)
D23: IC1.N05 (D23), IC2.42 (D23), J5.c18 (D23), J6.c18 (D23), J7.c18 (D23), J8.33 (DB7), J9.33 (DB7), J13.3 (DD7), U8.11 (B7), U28.45 (D7), U29.43 (SD7), U30.24 (IO_17), U32.11 (B7), U35.9 (A7)
D24: IC1.M05 (D24), IC2.40 (D24), J5.c16 (D24), J6.c16 (D24), J7.c16 (D24), J8.91 (D8), J9.91 (D8), J13.4 (DD8), U9.17 (B1), U22.11 (D0), U24.25 (D0), U25.44 (D0), U27.12 (D0), U28.41 (D8), U29.95 (SD8), U30.5 (IO_3), U35.18 (B0), U36.18 (B0)
D25: IC1.N04 (D25), IC2.39 (D25), J5.c15 (D25), J6.c15 (D25), J7.c15 (D25), J8.92 (D9), J9.92 (D9), J13.6 (DD9), U9.15 (B3), U22.13 (D1), U24.16 (D1), U25.45 (D1), U27.13 (D1), U28.39 (D9), U29.94 (SD9), U30.9 (IO_6), U35.17 (B1), U36.17 (B1)
D26: IC1.N03 (D26), IC2.38 (D26), J5.c14 (D26), J6.c14 (D26), J7.c14 (D26), J8.93 (D10), J9.93 (D10), J13.8 (DD10), U9.13 (B5), U22.14 (D2), U24.24 (D2), U25.46 (D2), U27.14 (D2), U28.37 (D10), U29.93 (SD10), U30.11 (IO_8), U35.16 (B2), U36.16 (B2)
D27: IC1.M04 (D27), IC2.37 (D27), J5.c13 (D27), J6.c13 (D27), J7.c13 (D27), J8.94 (D11), J9.94 (D11), J13.10 (DD11), U9.11 (B7), U22.15 (D3), U24.17 (D3), U25.47 (D3), U27.15 (D3), U28.35 (D11), U29.92 (SD11), U30.4 (IO_2), U35.15 (B3), U36.15 (B3)
D28: IC1.N02 (D28), IC2.36 (D28), J5.c12 (D28), J6.c12 (D28), J7.c12 (D28), J8.95 (D12), J9.95 (D12), J13.12 (DD12), U10.17 (B1), U22.17 (D4), U24.23 (D4), U25.48 (D4), U27.16 (D4), U28.33 (D12), U29.91 (SD12), U30.6 (IO_4), U35.14 (B4), U36.14 (B4)
D29: IC1.M03 (D29), IC2.35 (D29), J5.c11 (D29), J6.c11 (D29), J7.c11 (D29), J8.96 (D13), J9.96 (D13), J13.14 (DD13), U10.15 (B3), U22.19 (D5), U24.18 (D5), U25.1 (D5), U27.17 (D5), U28.31 (D13), U29.90 (SD13), U30.8 (IO_5), U35.13 (B5), U36.13 (B5)
D30: IC1.L04 (D30), IC2.34 (D30), J5.c10 (D30), J6.c10 (D30), J7.c10 (D30), J8.97 (D14), J9.97 (D14), J13.16 (DD14), U10.13 (B5), U22.20 (D6), U24.22 (D6), U25.2 (D6), U27.18 (D6), U28.29 (D14), U29.88 (SD14), U30.10 (IO_7), U35.12 (B6), U36.12 (B6)
D31: IC1.N01 (D31), IC2.33 (D31), J5.c9 (D31), J6.c9 (D31), J7.c9 (D31), J8.98 (D15), J9.98 (D15), J13.18 (DD15), U10.11 (B7), U22.22 (D7), U24.19 (D7), U25.3 (D7), U27.19 (D7), U28.27 (D15), U29.87 (SD15), U30.12 (IO_9), U35.11 (B7), U36.11 (B7)
FC0: IC1.D02 (FC0), U30.36 (IO_27), U39.61 (IO_46)
FC1: IC1.C01 (FC1), U30.37 (IO_28), U39.63 (IO_47)
FC2: IC1.D01 (FC2), U30.39 (IO_29), U39.64 (IO_48)
FPUCLK: IC2.11 (CLK), U20.4 (Y)
GND: BT1.2 (-), C1.2, C2.2, C3.2, C4.1, C5.1, C6.1, C7.2, C8.1, C9.2, C10.2, C11.2, C12.2, C13.2, C14.1, C15.1, C16.1, C17.2, C18.2, C19.2, C20.2, C21.1, C22.2, C23.1, C24.2, C25.1, C26.2, C27.2, C28.2, C29.2, C30.2, C31.2, C32.1, C33.2, C34.2, C35.2, C36.2, C37.2, C38.2, C39.2, C39#2.2, C40.2, C41.2, C42.2, C43.1, C44.1, C45.2, C46.1, C47.2, C48.2, C49.1, C50.1, C51.1, C52.1, C53.2, C54.2, C57.2, C58.2, C60.2, C61.1, C62.1, C63.2, C64.2, C65.2, C66.2, C67.2, C68.1, C69.1, C70.2, C71.2, C72.1, C73.1, C74.1, C75.2, C76.2, C77.2, C78.1, C79.1, C80.1, C81.1, C82.2, C83.2, C84.2, C85.2, C86.2, C87.2, C88.2, C89.2, C90.1, C91.2, C92.1, C93.2, C94.1, C95.1, C96.1, C97.2, C98.2, C99.2, C100.2, C101.2, C102.2, FB1.2, H1.1, H2.1, H3.1, H4.1, H5.1, H6.1, H7.1, H8.1, H9.1, IC1.C05 (GND@1), IC1.C07 (GND@2), IC1.C09 (GND@3), IC1.E03 (GND@4), IC1.E11 (GND@5), IC1.F03 (GND@6), IC1.G03 (GND@7), IC1.G11 (GND@8), IC1.J03 (GND@9), IC1.J11 (GND@10), IC1.L05 (GND@11), IC1.L07 (GND@12), IC1.L08 (GND@13), IC1.L09 (GND@14), IC2.5 (GND@1), IC2.6 (GND@2), IC2.7 (GND@3), IC2.8 (GND@4), IC2.9 (GND@5), IC2.12 (GND@6), IC2.14 (GND@7), IC2.19 (GND@8), IC2.30 (GND@9), IC2.41 (GND@10), IC2.51 (GND@11), IC2.63 (GND@12), J1.2, J1.10, J2.a1 (GND), J2.a10 (GND), J2.b1 (GND), J2.b5 (GND), J2.b10 (GND), J2.c1 (GND), J2.c10 (GND), J3.a1 (GND), J3.a10 (GND), J3.b1 (GND), J3.b5 (GND), J3.b10 (GND), J3.c1 (GND), J3.c10 (GND), J4.a1 (GND), J4.a10 (GND), J4.b1 (GND), J4.b5 (GND), J4.b10 (GND), J4.c1 (GND), J4.c10 (GND), J5.a1 (GND), J5.a5 (GND), J5.a14 (GND), J5.a23 (GND), J5.a32 (GND), J5.b1 (GND), J5.b2 (GND), J5.b5 (GND), J5.b14 (GND), J5.b23 (GND), J5.b32 (GND), J5.c1 (GND), J5.c8 (GND), J5.c17 (GND), J5.c26 (GND), J5.c28 (GND), J5.c32 (GND), J6.a1 (GND), J6.a5 (GND), J6.a14 (GND), J6.a23 (GND), J6.a32 (GND), J6.b1 (GND), J6.b2 (GND), J6.b5 (GND), J6.b14 (GND), J6.b23 (GND), J6.b32 (GND), J6.c1 (GND), J6.c8 (GND), J6.c17 (GND), J6.c26 (GND), J6.c28 (GND), J6.c32 (GND), J7.a1 (GND), J7.a5 (GND), J7.a14 (GND), J7.a23 (GND), J7.a32 (GND), J7.b1 (GND), J7.b2 (GND), J7.b5 (GND), J7.b14 (GND), J7.b23 (GND), J7.b32 (GND), J7.c1 (GND), J7.c8 (GND), J7.c17 (GND), J7.c26 (GND), J7.c28 (GND), J7.c32 (GND), J8.1 (GND), J8.10 (GND), J8.31 (GND), J8.80 (GND), J9.1 (GND), J9.10 (GND), J9.31 (GND), J9.80 (GND), J10.3 (GND), J10.5 (GND), J10.7 (GND), J10.15 (GND), J10.17 (GND), J10.18 (GND), J10.19 (GND), J10.24 (GND), J11.8, J11.11, J11.12, J11.15, J11.16, J11.17, J11.18, J11.24, J12.6, J13.2 (GND), J13.19 (GND), J13.22 (GND), J13.24 (GND), J13.26 (GND), J13.30 (GND), J13.40 (GND), J14.1 (GND), J14.3 (GND), J14.5 (GND), J14.7 (GND), J14.9 (GND), J14.11 (GND), J14.13 (GND), J14.15 (GND), J14.17 (GND), J14.19 (GND), J14.21 (GND), J14.23 (GND), J14.25 (GND), J14.27 (GND), J14.29 (GND), J14.31 (GND), J14.33 (GND), J15.5, J15.MH1, J15.MH2, J16.A3, J16.B3, J16.MH1, J16.MH2, J16.MH3, J16.MH4, J16.MH5, J17.13 (SHIELD), J17.R8 (GND), J18.2, J18.10, J19.2, J19.10, R4.1, R5.2, R7.1, R10.2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
GNDA: FB1.1, U22.45 (GNDA)
unnamed: D1.2 (A), RN8.4 (R3)
unnamed: J12.2, TP1.1
unnamed: J14.6 (NC/DRATE), U22.28 (DRATE0)
unnamed: J14.18 (~DIR), U22.56 (DIR)
unnamed: J14.14 (~DSA), U22.58 (DR0)
unnamed: J14.12 (~DSB), U22.62 (DR1)
unnamed: J14.34 (~DSKCHG), RN7.6 (R5), U22.31 (DSKCHG)
unnamed: J14.24 (~FWE), U22.52 (WGATE)
unnamed: J14.8 (~INDEX), RN7.2 (R1), U22.26 (INDEX)
unnamed: J14.10 (~MEA), U22.57 (MTR0)
unnamed: J14.16 (~MEB), U22.61 (MTR1)
unnamed: J14.30 (~RD), RN7.5 (R4), U22.41 (RDATA)
unnamed: J14.2 (~REDWC), U22.49 (DENSEL)
unnamed: J14.32 (~SIDE1), U22.51 (HDSEL)
unnamed: J14.20 (~STEP), U22.55 (STEP)
unnamed: J14.26 (~TRK00), RN7.3 (R2), U22.2 (TRK0)
unnamed: J14.28 (~WPT), RN7.4 (R3), U22.1 (WP)
unnamed: J14.22 (~WR), U22.53 (WDATA)
unnamed: J17.L4 (LEDG_A), RN8.2 (R1)
unnamed: J17.L1 (LEDY_A), RN8.3 (R2)
unnamed: C66.1, J17.R5 (RCT)
unnamed: C67.1, J17.R4 (TCT)
unnamed: U5.83 (INPUT/GCLK1), X1.3 (OUT)
unnamed: U15.1 (X1), Y1.1
unnamed: U15.2 (X2), Y1.2
unnamed: C43.2, U16.13 (XTAL1), Y2.2
unnamed: C44.2, U16.12 (XTAL2), Y2.1
unnamed: R3.2, U17.7 (VREF2), U17.8 (EN)
unnamed: U18#2.2 (A), U19.10 (CLK0)
unnamed: U19.9 (CLK1), U20.2 (A)
unnamed: U19.6 (CLK2), U21.2 (A)
unnamed: C45.1, U19.2 (XA), Y3.2
unnamed: C46.2, U19.3 (XB), Y3.1
unnamed: C51.2, U22.33 (XTAL1/CLK), Y4.1
unnamed: C52.2, U22.34 (XTAL2), Y4.2
unnamed: C55.1, U23.1 (C1+)
unnamed: C55.2, U23.3 (C1-)
unnamed: C56.1, U23.4 (C2+)
unnamed: C56.2, U23.5 (C2-)
unnamed: J15.3, U23.13 (R1IN)
unnamed: U23.12 (R1OUT), U24.31 (RXDA)
unnamed: U23.11 (T1IN), U24.30 (TXDA)
unnamed: J15.2, U23.14 (T1OUT)
unnamed: C59.2, U23.2 (VS+)
unnamed: C60.1, U23.6 (VS-)
unnamed: C57.1, U24.32 (X1/CLK), Y5.1
unnamed: C58.1, U24.33 (X2), Y5.2
unnamed: U25.40 (CLK), X2.3 (OUT)
unnamed: U26.1, U27.23 (P22)
unnamed: U26.3, U27.24 (P23)
unnamed: U26.5, U27.37 (P26)
unnamed: U26.9, U27.38 (P27)
unnamed: C64.1, U27.2 (XTAL1), Y6.2
unnamed: C65.1, U27.3 (XTAL2), Y6.1
unnamed: R7.2, U29.77 (BD7)
unnamed: R10.1, U29.96 (IOCS16B)
unnamed: C68.2, R9.1, U29.50 (X1), Y7.1
unnamed: C69.2, R9.2, U29.51 (X2), Y7.2
unnamed: U30.83 (INPUT/GCLK1), X3.3 (OUT)
unnamed: U34.21 (CLK), X4.3 (OUT)
unnamed: U39.83 (INPUT/GCLK1), X5.3 (OUT)
PWOK: J10.8 (PWR_OK), U16.29 (PC7)
PWR_LED: J11.14, U16.25 (PC3)
REFRESH: R1.2, U5.65 (IO_49), U15.7 (SQW/OUT)
R/~W: IC1.L03 (R/W\), IC2.28 (R/W\), J5.a10 (R/~W), J6.a10 (R/~W), J7.a10 (R/~W), U1.47 (~WE), U2.47 (~WE), U3.47 (~WE), U4.47 (~WE), U7.1 (A->B), U8.1 (A->B), U9.1 (A->B), U10.1 (A->B), U24.8 (R/W), U25.43 (R/W), U28.15 (R/~W), U30.30 (IO_22), U34.17 (R/~W), U35.1 (A->B), U39.55 (IO_41)
SIZ0: IC1.L02 (SIZ0), J5.a7 (SIZ0), J6.a7 (SIZ0), J7.a7 (SIZ0), U5.57 (IO_43), U39.58 (IO_44)
SIZ1: IC1.K03 (SIZ1), J5.a6 (SIZ1), J6.a6 (SIZ1), J7.a6 (SIZ1), U5.58 (IO_44), U39.60 (IO_45)
SMC_RX: J11.22, U16.14 (PD0)
SMC_TX: J11.20, U16.15 (PD1)
SYS_SCL: J5.c5 (SCL), J6.c5 (SCL), J7.c5 (SCL), J11.19, U11.12 (SCK), U12.12 (SCK), U15.6 (SCL), U16.22 (PC0), U17.6 (SCL2)
SYS_SDA: J5.c4 (SDA), J6.c4 (SDA), J7.c4 (SDA), J11.21, U11.13 (SDA), U12.13 (SDA), U15.5 (SDA), U16.23 (PC1), U17.5 (SDA2)
~8242CS: U27.6 (~CS), U40.7 (Y7)
~ADDECCFG: U16.5 (PB4), U39.75 (IO_56)
~AS: IC1.J02 (AS), IC2.21 (AS), J5.a13 (~AS), J6.a13 (~AS), J7.a13 (~AS), U5.52 (IO_39), U28.9 (~AS), U30.25 (IO_18), U34.16 (~AS), U39.52 (IO_39)
~ATA0CS: J13.37 (~CS0), U40.14 (Y1)
~ATA1CS: J13.38 (~CS1), U40.15 (Y0)
~ATAIRQ: J13.31 (INTRQ), U30.63 (IO_47)
~BGACK: IC1.C03 (BGACK), U34.11 (~BGACK)
~BG: IC1.B02 (BG), U34.62 (~BG)
~BR: IC1.A01 (BR), U34.63 (~BR)
~CPUHLT: IC1.H02 (HALT), U16.2 (PB1)
~CPURST: IC1.F12 (RESET), IC2.13 (RESET), U5.61 (IO_46), U11.18 (~RESET), U12.18 (~RESET), U16.1 (PB0), U30.70 (IO_53), U39.80 (IO_60)
~DCFGCS: U5.63 (IO_47), U38.11 (Y4)
~DMACCS: U34.19 (~CS), U38.10 (Y5)
~DMAIRQ: U30.60 (IO_45), U34.23 (~IRQ)
~DRAMCS: U5.64 (IO_48), U7.19 (CE), U8.19 (CE), U9.19 (CE), U10.19 (CE), U38.12 (Y3)
~DSACK0: IC1.F01 (DSACK0), IC2.31 (DSACK0), J5.a9 (~DSACK0), J6.a9 (~DSACK0), J7.a9 (~DSACK0), U5.55 (IO_41), U39.56 (IO_42)
~DSACK1: IC1.G02 (DSACK1), IC2.32 (DSACK1), J5.a8 (~DSACK1), J6.a8 (~DSACK1), J7.a8 (~DSACK1), U5.56 (IO_42), U39.57 (IO_43)
~DS: IC1.K02 (DS), IC2.20 (DS), J5.a12 (~DS), J6.a12 (~DS), J7.a12 (~DS), U5.54 (IO_40), U34.15 (~LDS/~DS), U39.54 (IO_40)
~EEPROMCS: U14.1 (~CS), U16.27 (PC5)
~ETHCS: U29.34 (AEN), U42.15 (Y0)
~FDDCS: U22.6 (~CS), U40.13 (Y2)
~FDDIRQ: U22.23 (~IRQ), U30.61 (IO_46)
~FPUCS: IC2.29 (CS), U38.13 (Y2)
~FWCS: U28.5 (~CS), U38.15 (Y0)
~IACK: J5.a3 (~IACK), J5.b3 (~PEACK), J6.a3 (~IACK), J6.b3 (~PEACK), J7.a3 (~IACK), J7.b3 (~PEACK), U24.37 (IACK), U25.37 (PC7/TIACK), U30.68 (IO_51), U34.22 (~IACK)
~IPL0: IC1.H13 (IPL0), U30.33 (IO_24)
~IPL1: IC1.G13 (IPL1), U30.34 (IO_25)
~IPL2: IC1.G12 (IPL2), U30.35 (IO_26)
~IRQ2: J8.4 (IRQ2), J9.4 (IRQ2), U30.40 (IO_30)
~IRQ3: J8.25 (IRQ3), J9.25 (IRQ3), U30.41 (IO_31)
~IRQ4: J8.24 (IRQ4), J9.24 (IRQ4), U30.44 (IO_32)
~IRQ5: J8.23 (IRQ5), J9.23 (IRQ5), U30.45 (IO_33)
~IRQ6: J8.22 (IRQ6), J9.22 (IRQ6), U30.46 (IO_34)
~IRQ7: J8.21 (IRQ7), J9.21 (IRQ7), U30.48 (IO_35)
~IRQ10: J8.65 (IRQ10), J9.65 (IRQ10), U30.49 (IO_36)
~IRQ11: J8.66 (IRQ11), J9.66 (IRQ11), U30.50 (IO_37)
~IRQ12: J8.67 (IRQ12), J9.67 (IRQ12), U30.51 (IO_38)
~IRQ14: J8.69 (IRQ14), J9.69 (IRQ14), U30.52 (IO_39)
~IRQ15: J8.68 (IRQ15), J9.68 (IRQ15), U30.54 (IO_40)
~KBIRQ: U27.35 (P24), U30.65 (IO_49)
~MSIRQ: U27.36 (P25), U30.64 (IO_48)
~PEP0EN: J5.a11 (~EN), U40.10 (Y5)
~PEP0IRQ: J5.a4 (~IRQ), U30.55 (IO_41)
~PEP1EN: J6.a11 (~EN), U40.11 (Y4)
~PEP1IRQ: J6.a4 (~IRQ), U30.56 (IO_42)
~PEP2EN: J7.a11 (~EN), U40.12 (Y3)
~PEP2IRQ: J7.a4 (~IRQ), U30.57 (IO_43)
~PERRST: J5.c3 (~CRST), J6.c3 (~CRST), J7.c3 (~CRST), J8.2 (RESET), J9.2 (RESET), J13.1 (~RST), U16.4 (PB3), U22.32 (RST), U24.34 (RESET), U25.39 (RESET), U27.4 (~RST), U29.33 (RSTDRV)
~PERR: J5.b4 (~PERR), J6.b4 (~PERR), J7.b4 (~PERR), U30.58 (IO_44)
~PICCS: U30.31 (IO_23), U38.9 (Y6)
~PSON: J10.16 (PS_ON#), RN6.5 (R4), U16.26 (PC4)
~PWR_SW: J11.9, RN6.2 (R1), U16.17 (PD3)
~RST_SW: J11.13, RN6.3 (R2), U16.3 (PB2)
~SMCCS: U16.16 (PD2), U38.14 (Y1)
~SMCRST: J12.5, R2.2, RN6.4 (R3), U16.9 (~RESET)
~TIMCS: U25.41 (CS), U42.14 (Y1)
~TIMER: U25.33 (PC3/TOUT), U30.67 (IO_50)
~UARTCS: U24.35 (CS), U40.9 (Y6)

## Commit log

2023-09-14 Updated README.md, Restructured directory tree
2023-09-15 Added symbol migrating script, Grammer check
2023-09-22 Modified system architecture, New KiCad Project: Cache Memory Module(SIMM80)
2023-11-14 Some Updates
2024-01-18 Large changes: EHBCSimpleEmu, kicad, fwcode, docs
    This commit contains some large changes:
    - Removed EHBCSimpleEmu (Moved to kms1212/llemu, kms1212/qemu)
    - (likely) Removed fwcode; now it only boots and stops
    - Modified documents
2024-01-18 Removed submodule "gcc-toolchain-builder"
